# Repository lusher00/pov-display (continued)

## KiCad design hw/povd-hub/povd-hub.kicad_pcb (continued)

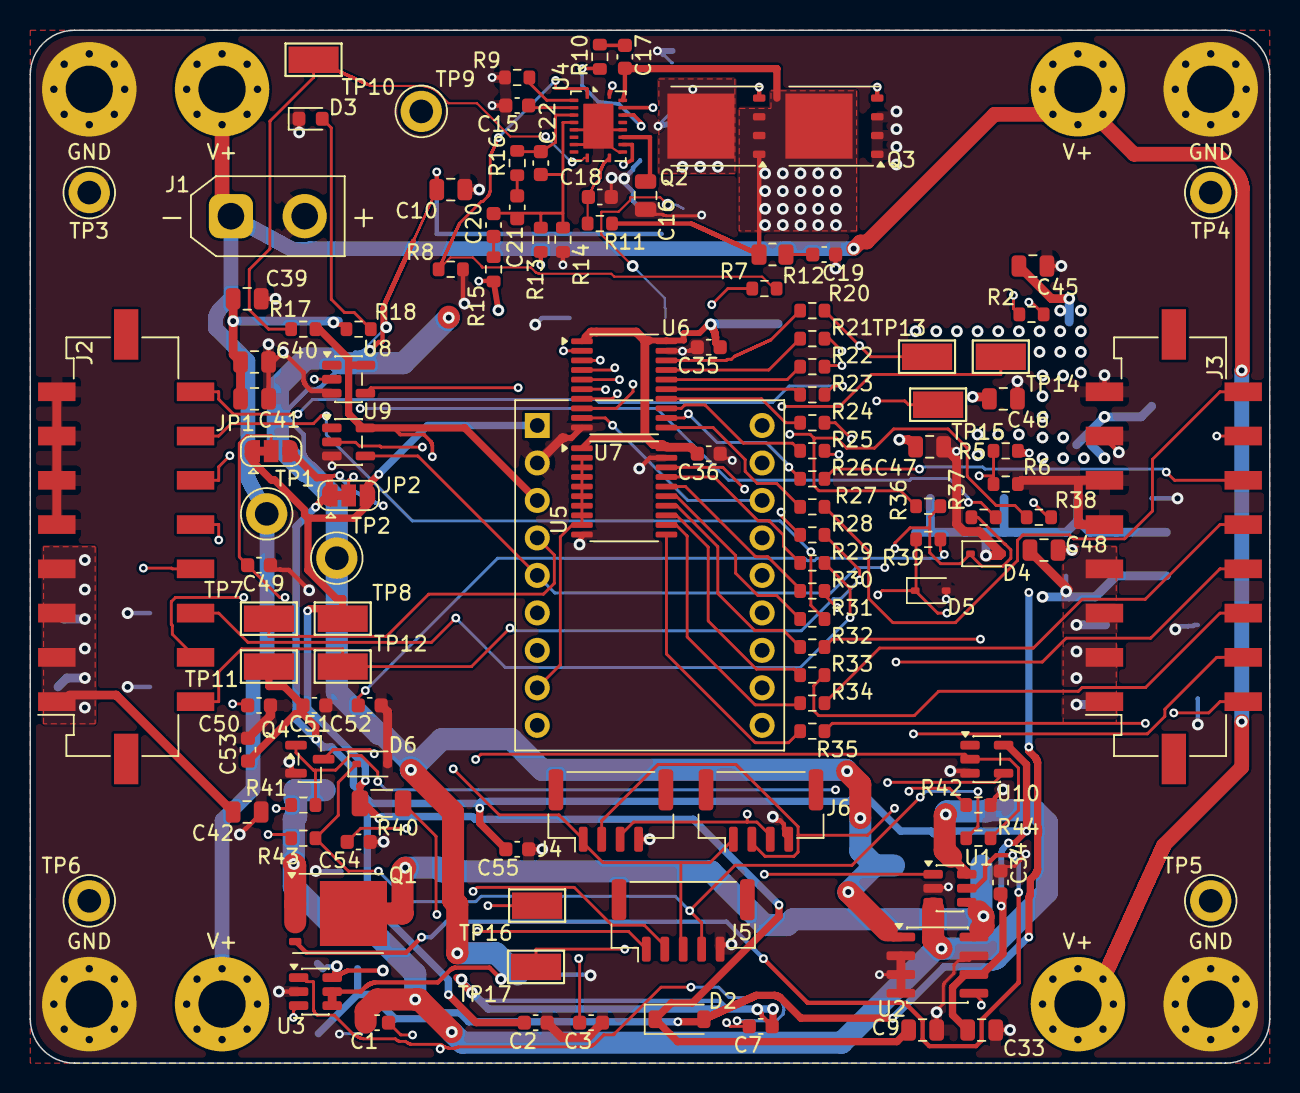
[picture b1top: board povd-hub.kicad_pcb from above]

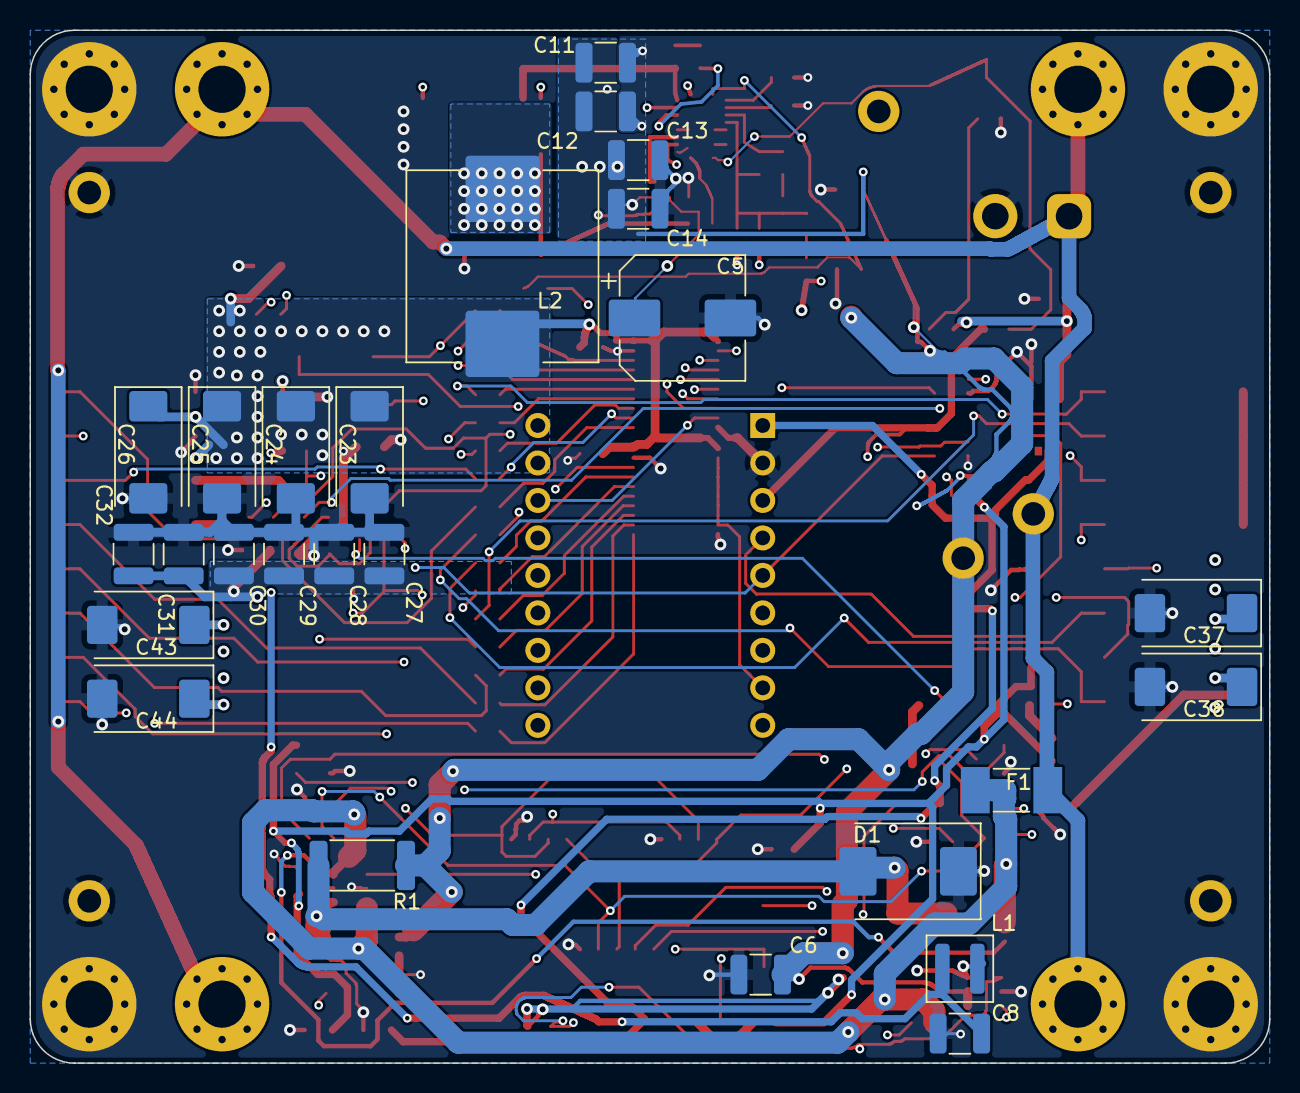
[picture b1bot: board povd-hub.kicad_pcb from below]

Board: 4 copper layers, 84.0 x 70.0 mm, 151 parts (26 on the bottom side), 90 nets.

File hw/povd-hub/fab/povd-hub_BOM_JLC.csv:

Comment,Designator,Footprint,LCSC Part #
100nF 25V X7R 0603,"C1,C7,C17",0603,C53084467
100nF 50V X7R 0603,"C2,C3,C34,C35,C36,C51,C53,C55",0603,C53084467
10uF 10V X5R 0805,"C9,C33,C39,C40,C41,C42,C45,C46,C47,C48",0805,C15850
1uF 100V X7R 0805,C10,0805,C105952
47nF 50V X7R 0603,C15,0603,C1622
2.2uF 16V X7R 0805,C16,0805,C377773
330pF 100V X7R 0603 (Yageo CC0603KRX7R0BB331),C19,0603,C576850
6.8nF 50V X7R 0603,C20,0603,C1631
12nF 50V X7R 0603,C21,0603,C107074
68pF 50V C0G 0603,C22,0603,C28262
1uF 16V X7R 0603,C49,0603,C15849
1nF 50V X7R 0603,"C50,C52",0603,C1588
B5819W,D2,SOD-123,C8598
Green LED 0603,D3,0603,C12065
PESD5V0S1BA,"D4,D5,D6",SOD-323,C19224
GH 4P,"J4,J6",JST GH BM04B-GHS-TBT,C161692
GH 5P OPT,J5,JST GH BM05B-GHS-TBT,C189891
BSC040N08NS5,"Q1,Q3",TDSON-8 (PG-TDSON-8),C534333
CSD19533Q5A,Q2,SON 5x6 (TDSON-8 land),C110197
AO3400A,Q4,SOT-23,C20917
1k 1% 0603,"R2,R37,R39,R43",0603,C21190
95.3k 1% 0603,R5,0603,C23267
16.9k 1% 0603,R6,0603,C227614
10k 1% 0603,"R7,R13,R17",0603,C25804
100k 1% 0603,"R8,R42",0603,C25803
24.9k 1% 0603,R9,0603,C25962
2.2R 1% 0603,R10,0603,C22939
360R 1% 0603,R11,0603,C25194
2.2R 0.5W 0805 anti-surge (Panasonic ERJ-P06J2R2V),R12,0805,C543414
1.91k 1% 0603,R14,0603,C22853
680R 1% 0603,R15,0603,C23228
11k 1% 0603,R16,0603,C25950
2.2k 1% 0603,R18,0603,C4190
33R 1% 0603,"R20,R21,R22,R23,R24,R25,R26,R27,R28,R29,R30,R31,R32,R33,R34,R35",0603,C23140
4.7k 1% 0603,"R36,R38",0603,C23162
47R 1% 1206,R40,1206,C17969
100R 1% 0603,"R41,R44",0603,C22775
Keystone 5015 test point,"TP7,TP8,TP10,TP11,TP12,TP13,TP14,TP15,TP16,TP17",Keystone 5015,C2906768
LM74700-Q1,U1,SOT-23-6,C2941042
INA240A3D,U2,SOIC-8,C2060584
LMR51610XDBVR,U3,SOT-23-6,C20539658
LM5145QRGYRQ1,U4,VQFN-20 3.5x4.5 (RGY),C3188678
74AHCT245PW,"U6,U7",TSSOP-20,C173388
74LVC1G17,"U8,U9,U10",SOT-23-5,C7836

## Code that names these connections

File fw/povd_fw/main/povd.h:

// povd hub firmware: shared definitions
#pragma once
#include <stdint.h>
#include <stdbool.h>

// ---- pins (povd-hub.kicad_pcb, U5 Waveshare ESP32-S3-Zero) ----
#define PIN_I_IN      1    // INA240 output, ADC1 channel 0
#define PIN_ENC_B     2
#define PIN_ENC_A     3
#define PIN_BUCK_EN   4    // high = 5 V / 15 A buck on
#define PIN_PCLK      5    // shared strip clock (LCD_CAM WR)
#define PIN_D0        6    // LCD_D0..D6 = IO6..IO12, LCD_D7 = IO13
#define PIN_DC        14   // i80 driver needs a D/C pin; IO14 is not connected on the hub
#define PIN_OPT_TX    43
#define PIN_OPT_RX    44

#define NUM_CH        8    // strip outputs: D0 -> DAT1 ... D7 -> DAT8
#define MAX_LEDS      256  // per channel (strips chained on one output count together)
#define MAX_COLS      1440

// ---- config: every field is a console key with the same name ----
typedef struct {
    int   blades;            // blades on the rotor, equally spaced
    int   strips_per_blade;  // channel c is blade c / strips_per_blade, strip c % strips_per_blade
    int   leds_per_strip;    // LEDs on one channel
    float led_pitch_mm;      // LED spacing along the strip
    float r0_mm;             // radius of the first LED in the chain
    int   strip_rev;         // 1 = chain starts at the tip
    int   columns_per_rev;   // angular resolution
    float clk_mhz;           // strip clock
    int   slots;             // pulse positions per rev on ENC_A (1 = one index pulse)
    int   missing;           // 1 = one position has no magnet: the pulse after the gap is angle 0
    float phase_deg;         // rotates the image
    int   mirror;            // 1 = flip rotation sense
    int   bright;            // SK9822 global brightness 0..31
    char  pattern[16];       // off index chan rings spokes grid wheel solid clock
    char  color[8];          // RRGGBB for pattern solid
    int   buck_boot;         // 1 = turn the 5 V buck on at boot
    float sim_rpm;           // >0: generate ENC_A pulses internally at this rpm (bench and QEMU)
    char  wifi_ssid[33];     // network to join; empty = WiFi off
    char  wifi_pass[65];
    char  hostname[32];      // mDNS name: http://<hostname>.local
} povd_config_t;

extern povd_config_t cfg;

// config.c
void config_defaults(void);
void config_load(void);
bool config_save(void);
void config_print(void);
// returns 0 ok, -1 unknown key, -2 bad value; *reconf set when the bus/buffers must be rebuilt
int  config_set(const char *key, const char *val, bool *reconf);
const char *const *config_keys(int *n);
int  config_json(char *buf, int size);          // all keys except wifi_pass, with type and range

// angle.c
typedef struct {
    bool     valid;      // rotor turning and (if missing=1) index seen
    float    frac;       // 0..1 angle since index
    float    rpm;
    uint32_t revs;
    uint32_t enc_a_edges, enc_b_edges;
} angle_t;
void angle_init(void);
void angle_get(angle_t *a);
void angle_sim_update(void);       // start/stop the internal pulse generator from cfg.sim_rpm

// leds.c
void leds_init(void);
void leds_reconfigure(void);       // pause output, rebuild bus and buffers, resume
uint64_t *leds_pixels(void);       // [col][byte k of the LED stream] -> 8 channel bytes
int  leds_stream_bytes(void);      // 4 * leds_per_strip
void leds_counters(uint32_t *cols, uint32_t *skipped);   // cumulative
float leds_t_column_us(void);

// render.c
void render(void);                 // fill leds_pixels() from cfg.pattern
void render_task_start(void);
void render_view(void);            // print the rendered image as colour blocks
void clock_set(int h, int m, int s);

// board.c
void board_init(void);
void buck_set(bool on);
bool buck_get(void);
int  i_in_mv(void);
bool uart_loopback(void);

// wifi.c, web.c
void wifi_start(void);                         // (re)connect with cfg.wifi_ssid / wifi_pass
void wifi_print(void);
const char *wifi_ip(void);
void web_start(void);
int  status_json(char *buf, int size);

// console.c
void console_start(void);
// set a config key (or buck / time) and apply it; 0 ok, else msg says why. Used by console and web.
int  povd_set(const char *key, const char *val, char *msg, int msg_size);
void status_print(void);
